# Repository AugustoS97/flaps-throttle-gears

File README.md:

# flaps-throttle-gears-pcb
PCB with ATMega for Flaps, Throttle and Gears for flight simulator

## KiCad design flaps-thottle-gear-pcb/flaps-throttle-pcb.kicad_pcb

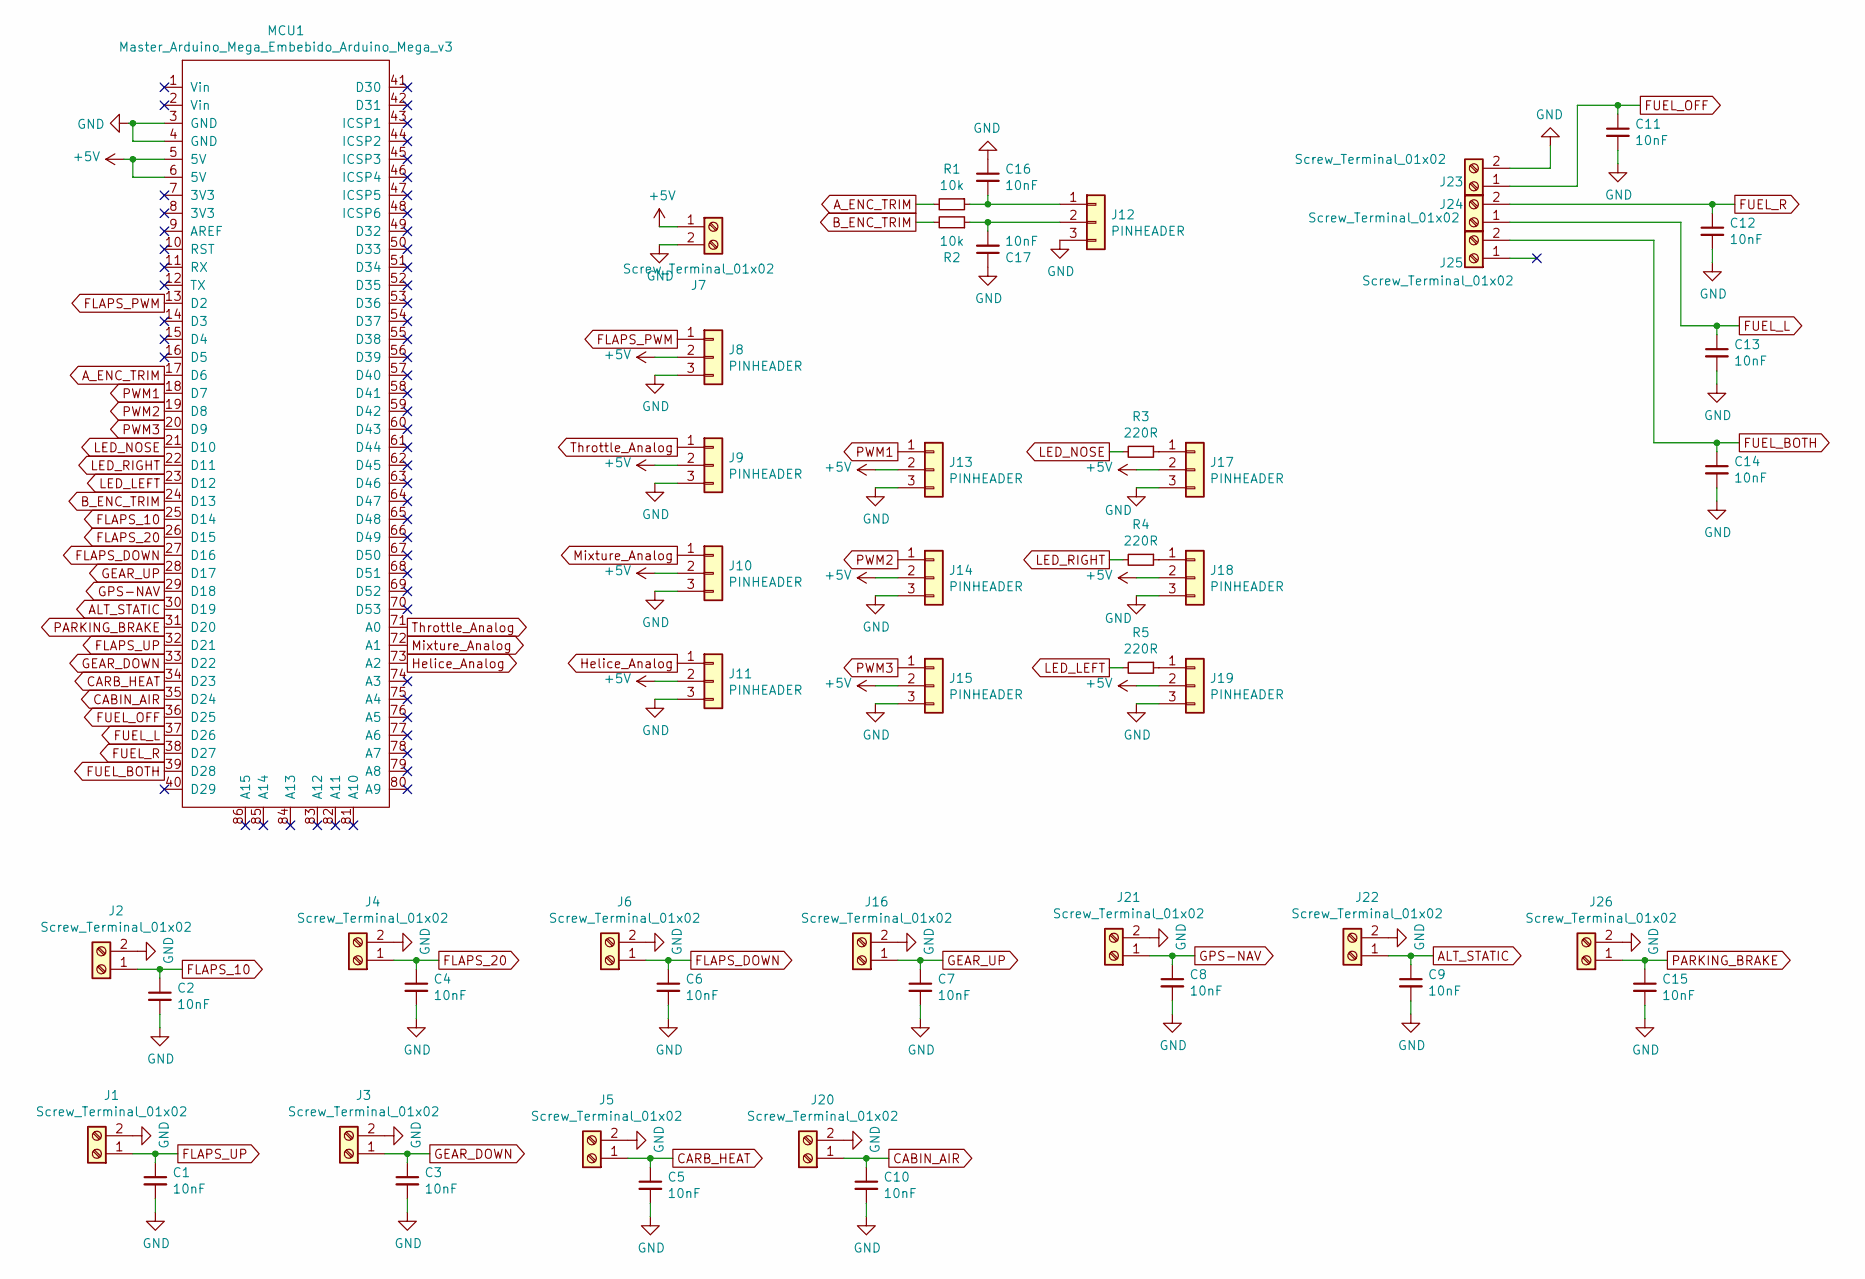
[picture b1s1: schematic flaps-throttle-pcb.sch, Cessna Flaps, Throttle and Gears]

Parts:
C1, C2, C3, C4, C5, C6, C7, C8, C9, C10, C11, C12, C13, C14, C15, C16, C17: 10nF; C_Disc_D3.8mm_W2.6mm_P2.50mm
J1, J2, J3, J4, J5, J6, J7, J16, J20, J21, J22, J23, J24, J25, J26: Screw_Terminal_01x02; TerminalBlock_bornier-2_P5.08mm
J8, J9, J10, J11, J12, J13, J14, J15, J17, J18, J19: PINHEADER; PinSocket_1x03_P2.54mm_Vertical
MCU1: Master_Arduino_Mega_Embebido_Arduino_Mega_v3; MEGA_Embebido
R1, R2: 10k; R_Axial_DIN0204_L3.6mm_D1.6mm_P7.62mm_Horizontal
R3, R4, R5: 220R; R_Axial_DIN0204_L3.6mm_D1.6mm_P7.62mm_Horizontal

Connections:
+5V: J7.1, J8.2, J9.2, J10.2, J11.2, J13.2, J14.2, J15.2, J17.2, J18.2, J19.2, MCU1.5 (5V), MCU1.6 (5V)
ALT_STATIC: C9.1, J22.1, MCU1.30 (D19)
A_ENC_TRIM: MCU1.17 (D6), R1.2
B_ENC_TRIM: MCU1.24 (D13), R2.2
CABIN_AIR: C10.1, J20.1, MCU1.35 (D24)
CARB_HEAT: C5.1, J5.1, MCU1.34 (D23)
FLAPS_10: C2.1, J2.1, MCU1.25 (D14)
FLAPS_20: C4.1, J4.1, MCU1.26 (D15)
FLAPS_DOWN: C6.1, J6.1, MCU1.27 (D16)
FLAPS_PWM: J8.1, MCU1.13 (D2)
FLAPS_UP: C1.1, J1.1, MCU1.32 (D21)
FUEL_BOTH: C14.1, J25.2, MCU1.39 (D28)
FUEL_L: C13.1, J24.1, MCU1.37 (D26)
FUEL_OFF: C11.1, J23.1, MCU1.36 (D25)
FUEL_R: C12.1, J24.2, MCU1.38 (D27)
GEAR_DOWN: C3.1, J3.1, MCU1.33 (D22)
GEAR_UP: C7.1, J16.1, MCU1.28 (D17)
GND: C1.2, C2.2, C3.2, C4.2, C5.2, C6.2, C7.2, C8.2, C9.2, C10.2, C11.2, C12.2, C13.2, C14.2, C15.2, C16.1, C17.1, J1.2, J2.2, J3.2, J4.2, J5.2, J6.2, J7.2, J8.3, J9.3, J10.3, J11.3, J12.3, J13.3, J14.3, J15.3, J16.2, J17.3, J18.3, J19.3, J20.2, J21.2, J22.2, J23.2, J26.2, MCU1.3 (GND), MCU1.4 (GND)
GPS-NAV: C8.1, J21.1, MCU1.29 (D18)
Helice_Analog: J11.1, MCU1.73 (A2)
LED_LEFT: MCU1.23 (D12), R5.2
LED_NOSE: MCU1.21 (D10), R3.2
LED_RIGHT: MCU1.22 (D11), R4.2
Mixture_Analog: J10.1, MCU1.72 (A1)
unnamed: C16.2, J12.1, R1.1
unnamed: C17.2, J12.2, R2.1
unnamed: J17.1, R3.1
unnamed: J18.1, R4.1
unnamed: J19.1, R5.1
PARKING_BRAKE: C15.1, J26.1, MCU1.31 (D20)
PWM1: J13.1, MCU1.18 (D7)
PWM2: J14.1, MCU1.19 (D8)
PWM3: J15.1, MCU1.20 (D9)
Throttle_Analog: J9.1, MCU1.71 (A0)

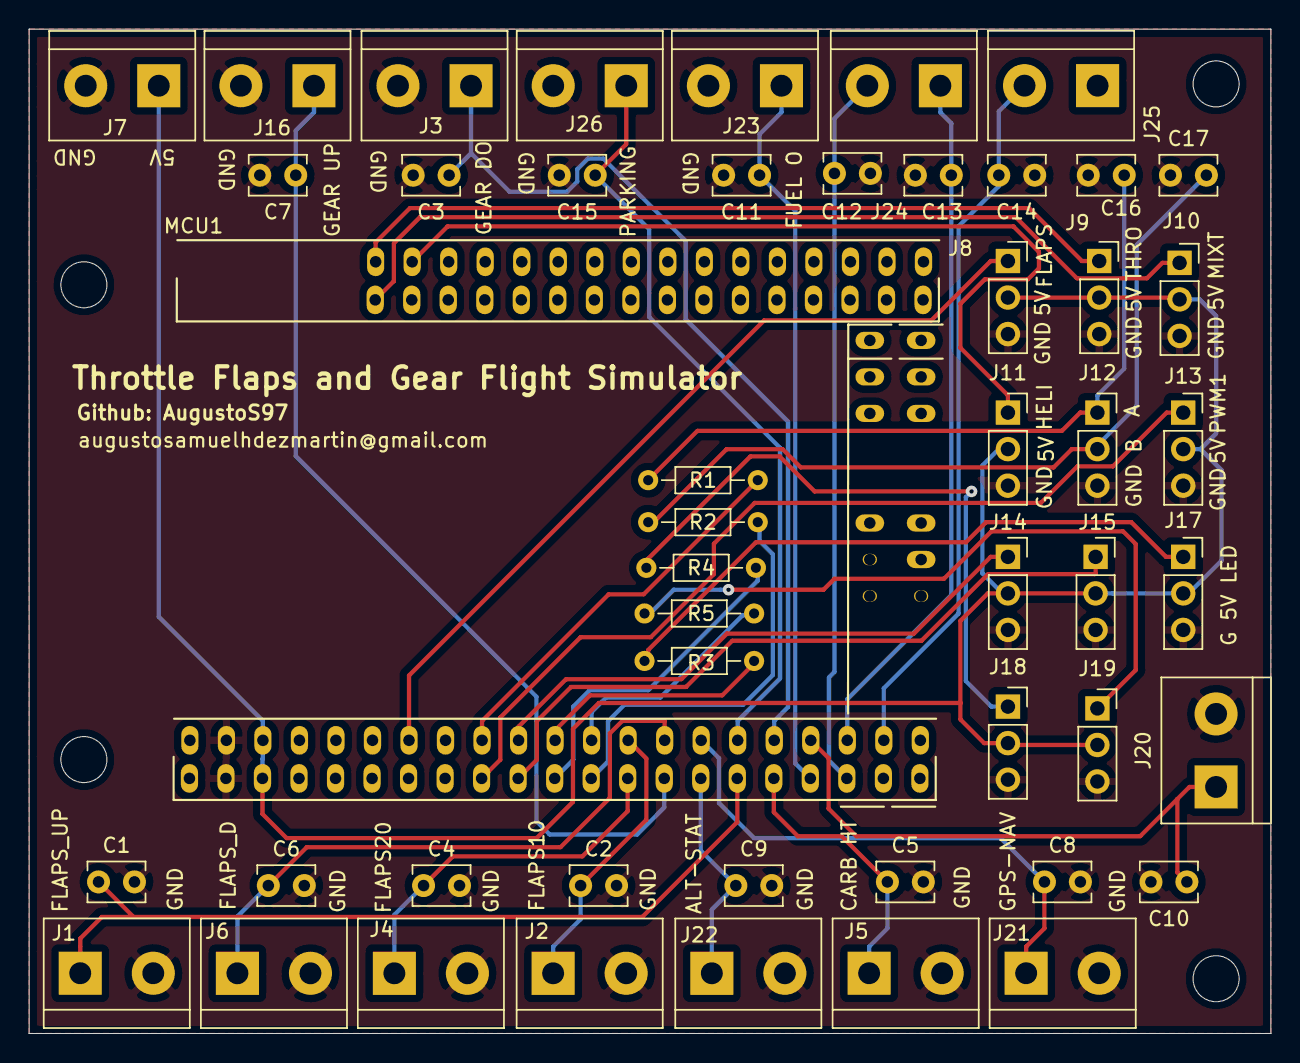
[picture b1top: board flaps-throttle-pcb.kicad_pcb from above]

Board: 2 copper layers, 86.4 x 69.9 mm, 53 parts (0 on the bottom side), 34 nets.

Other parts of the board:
h1, h2, h3, h4: MountingHole_3.2mm_M3

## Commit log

2021-10-09 Añadidos los ficheros del diseño de la PCB
2021-10-12 Añadidos los diseños del panel de Flaps, Tren, Parking y Trim.
